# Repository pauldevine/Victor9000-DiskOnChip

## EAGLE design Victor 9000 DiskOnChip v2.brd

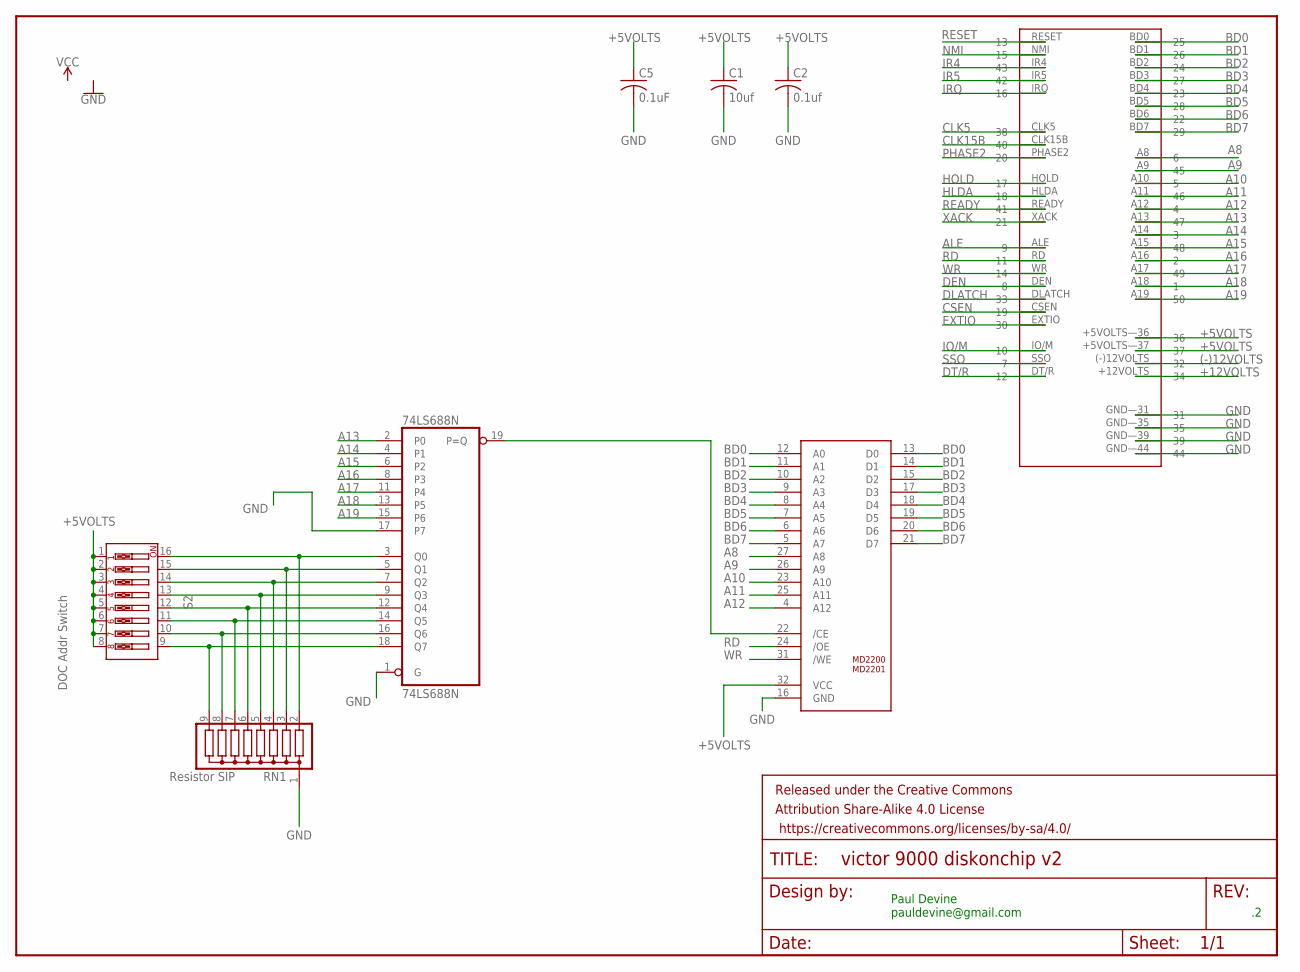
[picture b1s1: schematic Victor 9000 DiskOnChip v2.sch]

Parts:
74LS688N: 74LS688N; DIL20
C1: 10uf; C025-050X050
C2: 0.1uf; C025-050X050
C5: 0.1uF; C025-050X050
DISKONCHIP2000: DOC2000; DIL32
FRAME1: FRAME-LETTER; CREATIVE_COMMONS
RN1: Resistor SIP; SIL9
S2: DOC Addr Switch; DIPSWITCH-08
U$1: VICTOR_GOLD_FINGERS

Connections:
(-)12VOLTS: U$1.(-)12VOLTS (32)
+5VOLTS: C1.1, C2.1, C5.1, DISKONCHIP2000.32 (VCC), S2.1, S2.2, S2.3, S2.4, S2.5, S2.6, S2.7, S2.8, U$1.+5VOLTS—36 (36), U$1.+5VOLTS—37 (37)
+12VOLTS: U$1.+12VOLTS (34)
A8: DISKONCHIP2000.27 (A8), U$1.A8 (6)
A9: DISKONCHIP2000.26 (A9), U$1.A9 (45)
A10: DISKONCHIP2000.23 (A10), U$1.A10 (5)
A11: DISKONCHIP2000.25 (A11), U$1.A11 (46)
A12: DISKONCHIP2000.4 (A12), U$1.A12 (4)
A13: 74LS688N.2 (P0), U$1.A13 (47)
A14: 74LS688N.4 (P1), U$1.A14 (3)
A15: 74LS688N.6 (P2), U$1.A15 (48)
A16: 74LS688N.8 (P3), U$1.A16 (2)
A17: 74LS688N.11 (P4), U$1.A17 (49)
A18: 74LS688N.13 (P5), U$1.A18 (1)
A19: 74LS688N.15 (P6), U$1.A19 (50)
ALE: U$1.ALE (9)
BD0: DISKONCHIP2000.12 (A0), DISKONCHIP2000.13 (D0), U$1.BD0 (25)
BD1: DISKONCHIP2000.11 (A1), DISKONCHIP2000.14 (D1), U$1.BD1 (26)
BD2: DISKONCHIP2000.10 (A2), DISKONCHIP2000.15 (D2), U$1.BD2 (24)
BD3: DISKONCHIP2000.9 (A3), DISKONCHIP2000.17 (D3), U$1.BD3 (27)
BD4: DISKONCHIP2000.8 (A4), DISKONCHIP2000.18 (D4), U$1.BD4 (23)
BD5: DISKONCHIP2000.7 (A5), DISKONCHIP2000.19 (D5), U$1.BD5 (28)
BD6: DISKONCHIP2000.6 (A6), DISKONCHIP2000.20 (D6), U$1.BD6 (22)
BD7: DISKONCHIP2000.5 (A7), DISKONCHIP2000.21 (D7), U$1.BD7 (29)
CLK5: U$1.CLK5 (38)
CLK15B: U$1.CLK15B (40)
CSEN: U$1.CSEN (19)
DEN: U$1.DEN (8)
DLATCH: U$1.DLATCH (33)
DT/R: U$1.DT/R (12)
EXTIO: U$1.EXTIO (30)
GND: 74LS688N.1 (G), 74LS688N.10 (GND), 74LS688N.17 (P7), C1.2, C2.2, C5.2, DISKONCHIP2000.16 (GND), RN1.1, U$1.GND—31 (31), U$1.GND—35 (35), U$1.GND—39 (39), U$1.GND—44 (44)
HLDA: U$1.HLDA (18)
HOLD: U$1.HOLD (17)
IO/M: U$1.IO/M (10)
IR4: U$1.IR4 (43)
IR5: U$1.IR5 (42)
IRQ: U$1.IRQ (16)
unnamed: 74LS688N.18 (Q7), RN1.9, S2.9
unnamed: 74LS688N.16 (Q6), RN1.8, S2.10
unnamed: 74LS688N.14 (Q5), RN1.7, S2.11
unnamed: 74LS688N.12 (Q4), RN1.6, S2.12
unnamed: 74LS688N.9 (Q3), RN1.5, S2.13
unnamed: 74LS688N.7 (Q2), RN1.4, S2.14
unnamed: 74LS688N.5 (Q1), RN1.3, S2.15
unnamed: 74LS688N.3 (Q0), RN1.2, S2.16
unnamed: 74LS688N.19 (P=Q), DISKONCHIP2000.22 (/CE)
NMI: U$1.NMI (15)
PHASE2: U$1.PHASE2 (20)
RD: DISKONCHIP2000.24 (/OE), U$1.RD (11)
READY: U$1.READY (41)
RESET: U$1.RESET (13)
SSO: U$1.SSO (7)
VCC: 74LS688N.20 (VCC)
WR: DISKONCHIP2000.31 (/WE), U$1.WR (14)
XACK: U$1.XACK (21)

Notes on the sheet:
Paul Devine pauldevine@gmail.com

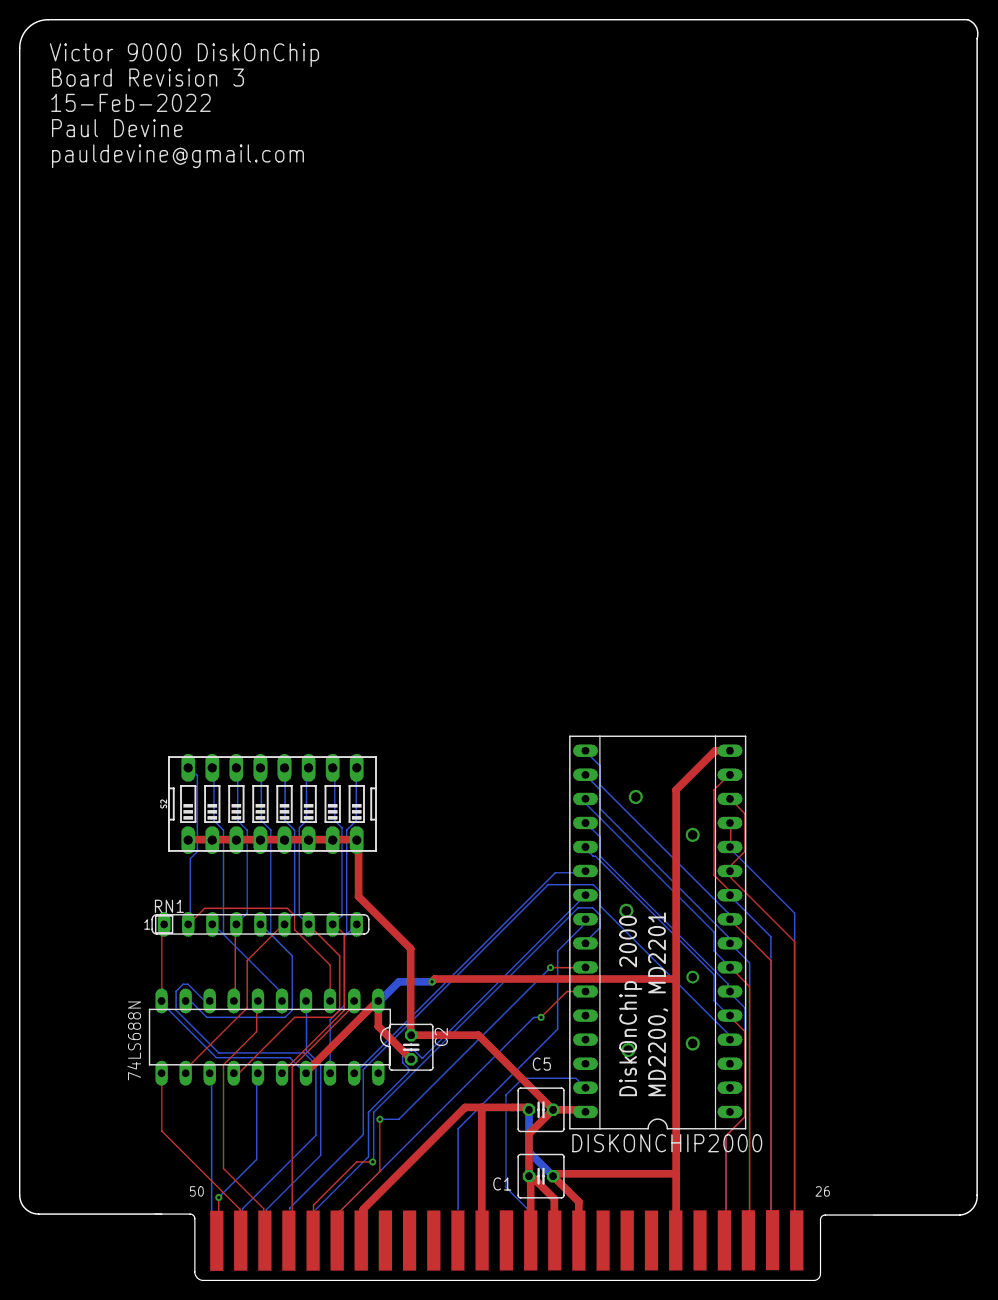
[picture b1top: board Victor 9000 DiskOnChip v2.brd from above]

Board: 2 copper layers, 101.1 x 133.0 mm, 9 parts (0 on the bottom side), 33 nets.

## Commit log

2022-01-12 rebuliding board, adding capacitors
2022-01-12 cleaned up schematic
2022-01-12 Cleaned up some routing
2022-01-27 fixed capacitors to be through hole rather than SMD
2022-03-02 adjusted gold fingers to be slightly thinner to prevent short circuit
2022-03-07 adding PDF of schematic and board

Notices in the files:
parts and their libraries:
SparkFun-Aesthetics: Licensing: Creative Commons ShareAlike 4.0 International - https://creativecommons.org/licenses/by-sa/4.0
SparkFun-Aesthetics: Released under the Creative Commons Attribution Share-Alike 4.0 License
SparkFun-Aesthetics: https://creativecommons.org/licenses/by-sa/4.0
